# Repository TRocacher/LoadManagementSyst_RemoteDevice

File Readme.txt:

Branche DevRTC_StdBy_LL

-> Le développement HAL standby et RTC est un échec, le processeur est bricked car endormi à jamais...
nRST et VCC sont en CC sérieux. Voir de plus près.
-> Jusque là le code est vite lourd, 40% facile sans avoir trop rien fait...

Dans cette branche, on essaie de voir la conception en LL pour diminuer le code

Le répertoire de travail est /ExploreCodeStdby/MyNucleoL476_StdByPower

On crée un répertoire à partir de cube, en conception LL.
On va chercher l'exemple LL :
C:\Users\trocache\STM32Cube\Repository\STM32Cube_FW_L4_V1.17.2\Projects\NUCLEO-L476RG\Examples_LL\PWR\PWR_EnterStandbyMode

On récupère les 3 src et les 3 inc, que l'on copie dans le projet juste créé (remplacement de ceux créés par cube).
Compilation OK
SRC :
main.c 
stm32l4xx_it.c
system_stm32l4xx.c (est le même)

INC
main.h
stm32_assert.h
stm32l4xx_it.h

OBJ 1 : on fait idem mais périodique avec le wakeup timer.
OBJ 2 : faire tourner l'I2C en LL.

****************************
50abc65 
OBJ 1 en cours, bac à sable ajouté pour récupérer des codes générés automatiquement Cube.
/MyNucleoL476_StdByPower modifié, inspiré de RTC_ExitStandbyWithWakeUpTimer
A faire : Bien lire et faire une synthèse sur wakeup RTC Standby

****************************
349ff09
/ExploreCodeStdby / BacASable_LLFromCube
				  / MyNucleoL476_StdByPower
Programme opérationnel en standby mode !
		* PWR reset : LED s'allume 5s
		* nRST : LED s'allume 2s
		* standby wake up : LED s'allume 200ms

****************************
35642cd		
/ExploreCodeStdby / Remote_L041_StdByPower

Même programme sur 32L041F6P7
Programme opérationnel en standby mode !
		* PWR reset : PA1 (LEDIR) on 6s
		* nRST : PA1 (LEDIR) on  3s
		* standby wake up : PA1 (LEDIR) on  1s
		
Le tout sur le proto n°1 fait pas José.

****************************
2902111    
/ExploreCodeStdby / Remote_L041_StdByPower

Le programme fais une émission en boucle UART via FSK. Fonctionne à 38400 Bds, test en réception avec la carte tecom 103 de 4IS.
OK.
A faire réception.

62a0048 
/ExploreCodeStdby / Remote_L041_StdByPower
Pgm en IT à 9600 Bds, émetteur = RT606 et PC via XCTU. 
Voir main.c pour l'explication fin.
A ce stade, RxCmde, TxCmde, CD, Tx, Rx testés.

****************************	
b0ee319 
/ExploreCodeStdby / Remote_L041_StdByPower
Validation User BP en IT front descendant.

****************************
Après b0ee319 
ATTENTION CHANGEMENT REP ICI : /ExploreCodeStdby / BacASable_L041
Validation ADC mais soucis sur l'alimentation. Parasite important rayonné et conduit (20mV 100k à 30k)
qui parasite complètement l'ADC...

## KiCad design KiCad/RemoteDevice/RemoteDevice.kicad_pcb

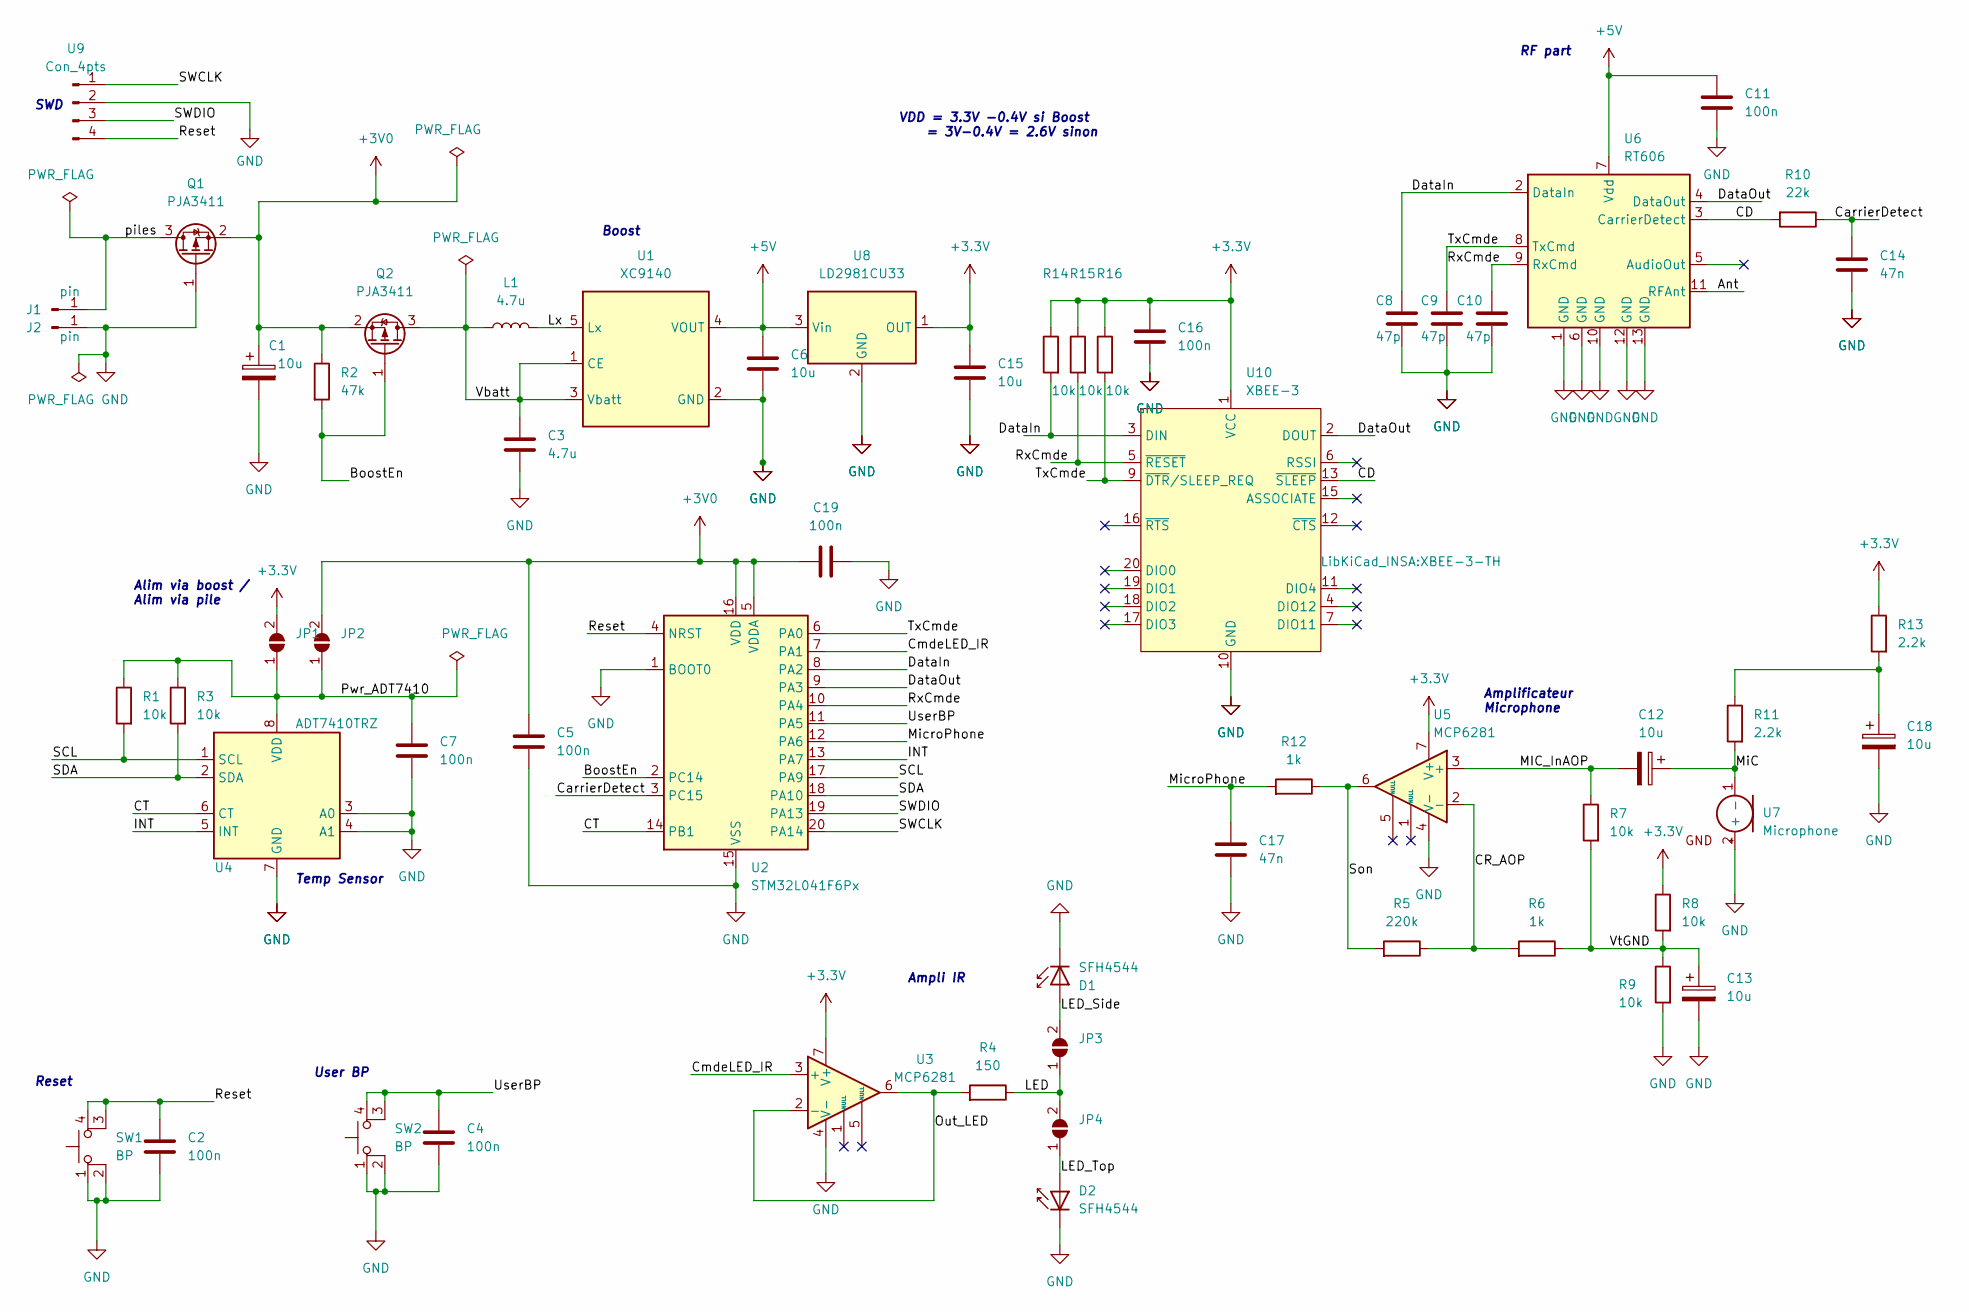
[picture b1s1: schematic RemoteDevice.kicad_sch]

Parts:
C1, C12, C13, C18: 10u; CP_EIA-7132-20_AVX-U
C2, C4, C5, C7, C11, C16, C19: 100n; C_1206_3216Metric
C3: 4.7u; C_1812_4532Metric
C6, C15: 10u; C_1812_4532Metric
C8, C9, C10: 47p; C_0805_2012Metric
C14, C17: 47n; C_1206_3216Metric
D1, D2: SFH4544; LED_D5.0mm_IRGrey
J1, J2: pin; PinHeader1Pt
JP1, JP2, JP3, JP4: SolderJumper_2_Open; SolderJumper-2_P1.3mm_Open_TrianglePad1.0x1.5mm
L1: 4.7u; L_Abracon_ASPI-3012S
Q1, Q2: PJA3411; SOT-23
R1, R3, R7, R8, R9, R14, R15, R16: 10k; R_1206_3216Metric
R2: 47k; R_1206_3216Metric
R4: 150; R_1206_3216Metric
R5: 220k; R_1206_3216Metric
R6, R12: 1k; R_1206_3216Metric
R10: 22k; R_1206_3216Metric
R11, R13: 2.2k; R_1206_3216Metric
SW1, SW2: BP; SW
U1: XC9140; SOT-23-5
U2: STM32L041F6Px; TSSOP-20_4.4x6.5mm_P0.65mm
U3, U5: MCP6281; SOIC-8_3.9x4.9mm_P1.27mm
U4: ADT7410TRZ; SOP-8_3.9x4.9mm_P1.27mm
U6: RT606
U7: Microphone
U8: LD2981CU33; SOT-89-3_Handsoldering
U9: Con_4pts; PinHeader4pts
U10: XBEE-3; XBEE-3-TH

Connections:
+3V0: C1.1, C5.1, C19.1, JP2.2 (B), Q1.2 (S), Q2.2 (S), R2.1, U2.5 (VDDA), U2.16 (VDD)
+3V3: C15.1, C16.1, JP1.2 (B), R8.1, R13.1, R14.1, R15.1, R16.1, U3.7 (V+), U5.7 (V+), U8.1 (OUT), U10.1 (VCC)
+5V: C6.1, C11.1, U1.4 (VOUT), U6.7 (Vdd), U8.3 (Vin)
/Ant: U6.11 (RFAnt)
/BoostEn: Q2.1 (G), R2.2, U2.2 (PC14)
/CD: R10.2, U6.3 (CarrierDetect), U10.13 (~SLEEP)
/CR_AOP: R5.1, R6.2, U5.2 (-)
/CT: U2.14 (PB1), U4.6 (CT)
/CarrierDetect: C14.1, R10.1, U2.3 (PC15)
/CmdeLED_IR: U2.7 (PA1), U3.3 (+)
/DataIn: C8.1, R14.2, U2.8 (PA2), U6.2 (DataIn), U10.3 (DIN)
/DataOut: U2.9 (PA3), U6.4 (DataOut), U10.2 (DOUT)
/INT: U2.13 (PA7), U4.5 (INT)
/LED: JP3.1 (A), JP4.2 (B), R4.1
/LED_Side: D1.2 (A), JP3.2 (B)
/LED_Top: D2.2 (A), JP4.1 (A)
/Lx: L1.1, U1.5 (Lx)
/MIC_InAOP: C12.2, R7.1, U5.3 (+)
/MiC: C12.1, R11.2, U7.1 (-)
/MicroPhone: C17.1, R12.2, U2.12 (PA6)
/Out_LED: R4.2, U3.2 (-), U3.6
/Pwr_ADT7410: C7.1, JP1.1 (A), JP2.1 (A), R1.1, R3.1, U4.8 (VDD)
/Reset: C2.1, SW1.3, SW1.4, U2.4 (NRST), U9.4
/RxCmde: C10.1, R15.2, U2.10 (PA4), U6.9 (RxCmd), U10.5 (~RESET)
/SCL: R1.2, U2.17 (PA9), U4.1 (SCL)
/SDA: R3.2, U2.18 (PA10), U4.2 (SDA)
/SWCLK: U2.20 (PA14), U9.1
/SWDIO: U2.19 (PA13), U9.3
/Son: R5.2, R12.1, U5.6
/TxCmde: C9.1, R16.2, U2.6 (PA0), U6.8 (TxCmd), U10.9 (~DTR/SLEEP_REQ)
/UserBP: C4.1, SW2.3, SW2.4, U2.11 (PA5)
/Vbatt: C3.1, L1.2, Q2.3 (D), U1.1 (CE), U1.3 (Vbatt)
/VtGND: C13.1, R6.1, R7.2, R8.2, R9.1
/piles: J1.1, Q1.3 (D)
GND: C1.2, C2.2, C3.2, C4.2, C5.2, C6.2, C7.2, C8.2, C9.2, C10.2, C11.2, C13.2, C14.2, C15.2, C16.2, C17.2, C18.2, C19.2, D1.1 (K), D2.1 (K), J2.1, Q1.1 (G), R9.2, SW1.1, SW1.2, SW2.1, SW2.2, U1.2 (GND), U2.1 (BOOT0), U2.15 (VSS), U3.4 (V-), U4.3 (A0), U4.4 (A1), U4.7 (GND), U5.4 (V-), U6.1 (GND), U6.6 (GND), U6.10 (GND), U6.12 (GND), U6.13 (GND), U7.2 (+), U8.2 (GND), U9.2, U10.10 (GND)
unnamed: C18.1, R11.1, R13.2

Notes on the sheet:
Ampli IR
Boost
Reset
RF part
Alim via boost / Alim via pile
Amplificateur Microphone
VDD = 3.3V -0.4V si Boost = 3V-0.4V = 2.6V sinon
Temp Sensor
User BP
SWD

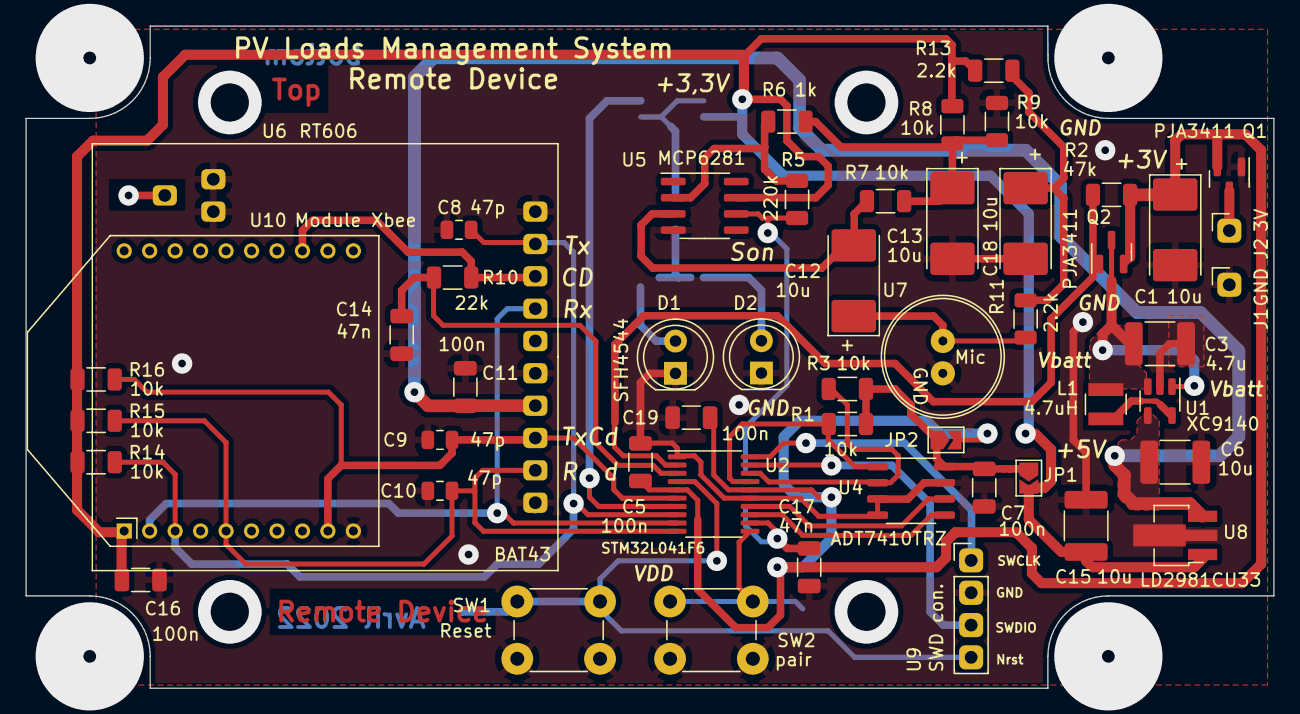
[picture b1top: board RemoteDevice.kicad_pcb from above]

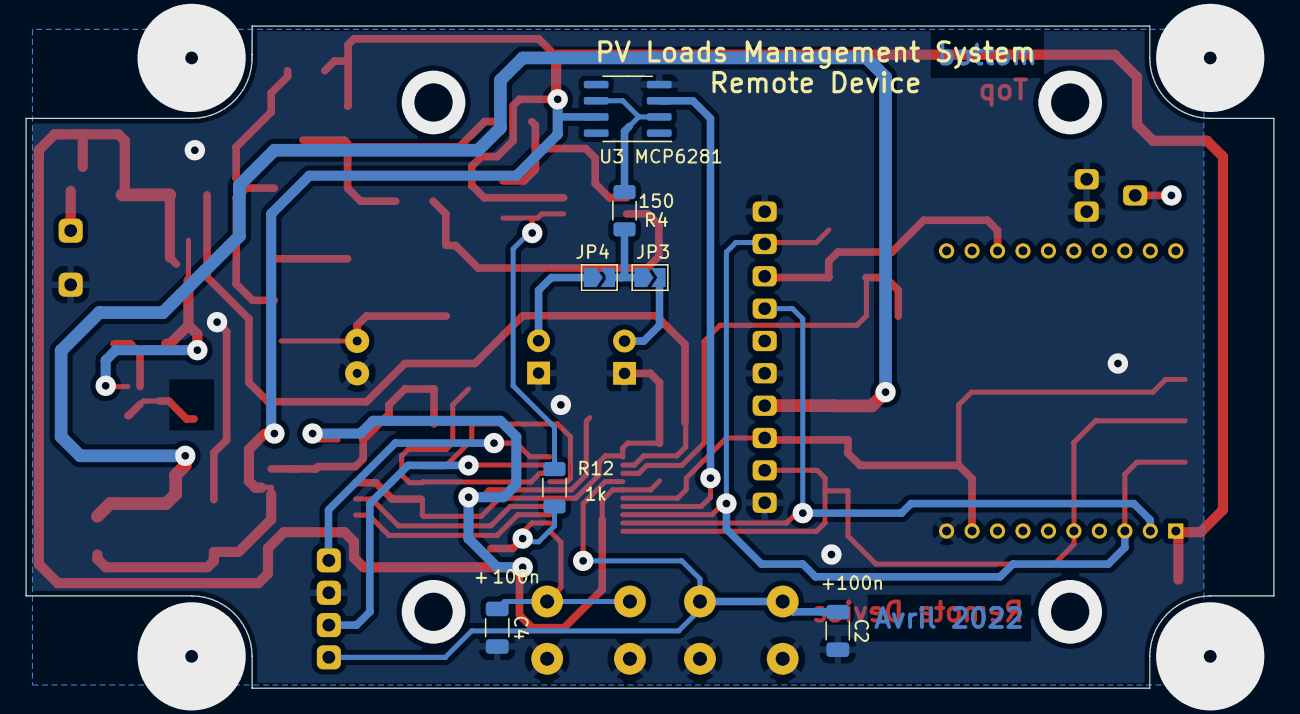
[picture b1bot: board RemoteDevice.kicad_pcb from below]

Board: 2 copper layers, 98.0 x 52.0 mm, 58 parts (7 on the bottom side), 35 nets.

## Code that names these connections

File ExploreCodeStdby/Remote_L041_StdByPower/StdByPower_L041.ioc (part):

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PA0-CK_IN.GPIO_Label=TxCmde
PA0-CK_IN.GPIOParameters=GPIO_Label
PA6.Mode=IN6
PA10.Mode=I2C
Mcu.UserName=STM32L041F6Px
PC14-OSC32_IN.Signal=GPIO_Output
PC15-OSC32_OUT.GPIO_Label=CD
RCC.SYSCLKSource=RCC_SYSCLKSOURCE_PLLCLK
PA3.Mode=Asynchronous
PA13.Signal=SYS_SWDIO
PA9.Mode=I2C
PA9.Signal=I2C1_SCL
PC15-OSC32_OUT.Signal=GPIO_Input
PA1.Signal=GPIO_Output
PA5.Signal=GPXTI5
RCC.HSE_VALUE=8000000
board=custom
PA0-CK_IN.Signal=GPIO_Output
PA1.GPIOParameters=GPIO_Label
PA14.Mode=Serial_Wire
PB1.GPIO_Label=CT
PA1.GPIO_Label=LED_IR
PA4.GPIOParameters=GPIO_Label
PA13.Mode=Serial_Wire
Mcu.Name=STM32L041F6Px
PC14-OSC32_IN.GPIOParameters=GPIO_Label
PA2.Signal=USART2_TX
PA4.Signal=GPIO_Output
RCC.SYSCLKFreq_VALUE=24000000
Mcu.Package=TSSOP20
PA6.Signal=ADC_IN6
PB1.Signal=GPIO_Input
PA7.GPIO_Label=INT
PA5.GPIO_Label=User_BP
PA10.Signal=I2C1_SDA
PA14.Signal=SYS_SWCLK
PA5.GPIOParameters=GPIO_Label
PA2.Mode=Asynchronous
PC14-OSC32_IN.GPIO_Label=Boost_En
PC15-OSC32_OUT.GPIOParameters=GPIO_Label
PA4.GPIO_Label=RxCmde
PA7.GPIOParameters=GPIO_Label
PA3.Signal=USART2_RX
PB1.GPIOParameters=GPIO_Label
PA7.Signal=GPIO_Input

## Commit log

2022-04-21 Kicad correspond à le varsion GEI du 21 04 2022. Cube IDE démarré avec la cible STM32L041F6. I2C demarré, Cube Mx OK IO sauf TIM2 Ch2 (IR)
2022-04-25 I2C Temperature OK sur Remote Device. Rem : code très lourd déjà plus de 50% !
2022-04-26 RTC HAL débuté. La RTC tourne à 1 Hz, le calendar évolue bien. La LSI est assez précise. La lecture HAL merde. Création Aide RTC txt.
2022-05-06 Migration example ST Pwr Stdby vers rep local, developpement LL. Code qui tourne sur nucléo 476RG conformément à l'exemple
2022-05-07 avancement du programme : à terminer pour un réveil toutes les 5 secondes.
2022-05-14 Stand by mode OK sur L476. Voir readme pour plus d'info. NB : un petit cours a été démarré /system/LowPowerSTM32_v3.odt
2022-05-15 standby OK sur proto Remote Device L041. Test sur LED IR, PA1. Voir readme pour les détails
2022-05-19 validation RT606 en émission 38400 Bds, validation aussi du boost
2022-05-22 Validation RT606 en réception, 9600 Bds via PC et XCTU. Vérif ligne CD via scope
2022-05-22 Validation IT externe user BP OK
2022-05-23 Validation ADC (trigger TIM22, DMA loupée avec Cube, possible qu'il manque juste un start DMA... Soucis avec bruit du boost
2022-06-07 début amélioration PCB, ajout du txt précisant les modifs, mise à jour des documents constructeurs
2022-06-09 modifs schéma faites, reste à faire l'association pour la netlist. Il manque aussi le Xbee
2022-06-10 schéma finalisé, prise en compte des modifs indiquées dans AfairePCB.txt. Prêt pour nouveau PCB
2022-06-12 routage commencé. ALim OK placer les deux diodes, étudier l'alim particulière uC et Temp Sensor
2022-06-13 Reste la partie Xbee et les résistances de pull up. Bien penser aussi les plans de masse alim...
2022-06-19 Routage presque fini, reprendre la partie bottom en niveau de la sériegraphie
2022-06-20 routage terminé, proto à envoyer à José
2022-06-20 Routage revu (tailles condensateur sur switchs). Version envoyée à José le 20 06 2022
2022-06-30 schéma revu avec quelques valeurs retouchées : val correspondent à l'assemblage. Board non mis à jour pour si peu. Le silkscreen est modifié par contre
2022-06-30 Version OK température, la dernière taggée configure le capteur en low power
2022-07-01 Version modifié : ajout pull up RT606 pour adapt niveau, supression BAT43, ajout capa de découplage uC. A tester
